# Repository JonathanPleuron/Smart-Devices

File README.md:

## Smart Gas Sensor

This project was realised in the IoT growing context. It introduces a solution of 
smart gas sensor using the emerging LoRa technology.

### Code 

See the arduino section for the sensor relative implementation (low level).
See the JAVA section for application (high level).

### Documentation

See documentation folder for global documentation about the project and useful datasheets

### PCB

A PCB was designed for the Smart sensor (Uses [KiCad](http://kicad-pcb.org/) free software)

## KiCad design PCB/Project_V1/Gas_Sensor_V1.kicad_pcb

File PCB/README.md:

## PCB conception

The PCB for the projet "Smart gas sensor" was designed using the free software Kicad.

### Presentation

See PCB_Kicad.pdf

### Sources

The available sources are :

	- Project_V1 : Kicad source files (Schematic, footprints, Netlist, PCB)
	- MyLib : Library for specifically designed components

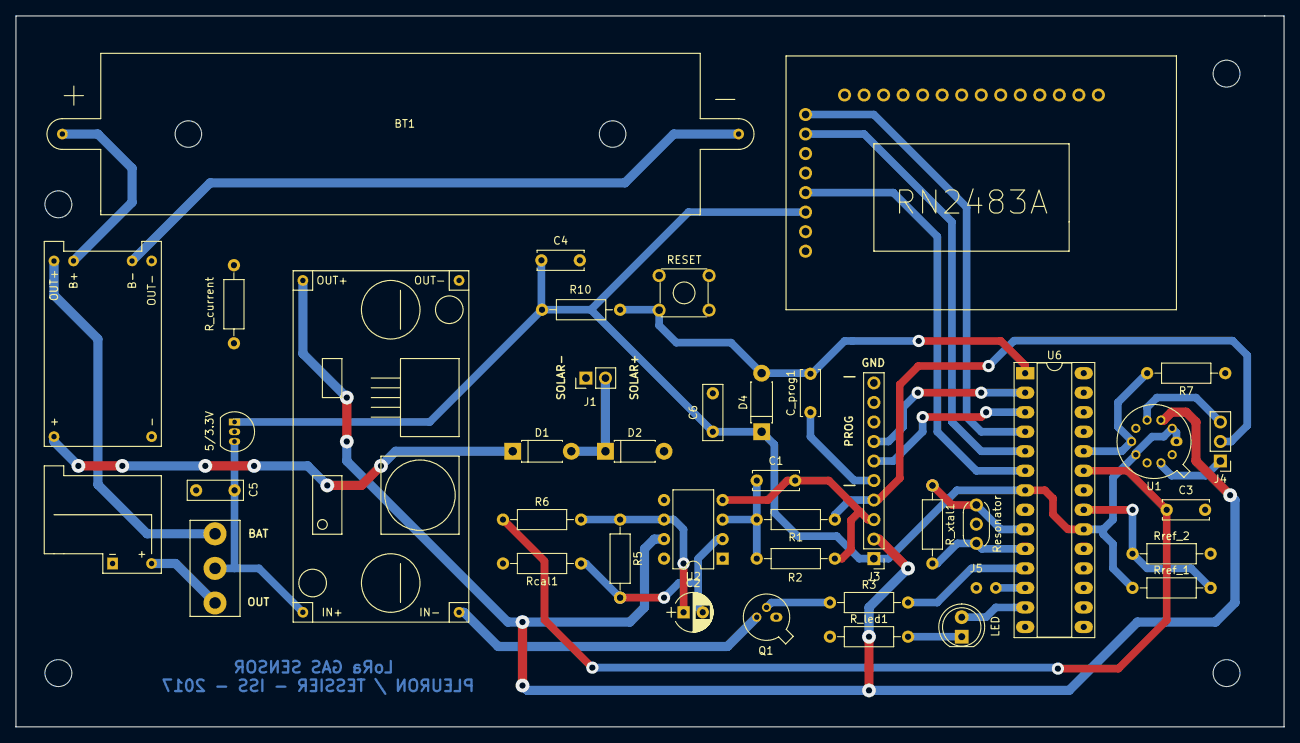
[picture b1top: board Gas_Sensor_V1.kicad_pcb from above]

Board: 2 copper layers, 165.0 x 92.5 mm, 38 parts (0 on the bottom side), 29 nets.

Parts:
5/3.3V: L78L33_TO92; TO-92_Inline_Narrow_Oval
BT1: 3.6V; BatterieSupport
C1, C3, C4: 100n; C_Disc_D6.0mm_W2.5mm_P5.00mm
C2: 1u; CP_Radial_D5.0mm_P2.50mm
C5: 330n; C_Rect_L7.2mm_W2.5mm_P5.00mm_FKS2_FKP2_MKS2_MKP2
C6: 100n; C_Rect_L7.2mm_W2.5mm_P5.00mm_FKS2_FKP2_MKS2_MKP2
C_prog1: 100n; C_Disc_D6.0mm_W2.5mm_P5.00mm
D1, D2: D; D_DO-41_SOD81_P7.62mm_Horizontal
D4: D_DO-41_SOD81_P7.62mm_Horizontal
J1: Socket_Strip_Straight_1x02_Pitch2.54mm
J3: Socket_Strip_Straight_1x10_Pitch2.54mm
J4: Pin_Header_Straight_1x03_Pitch2.54mm
J5: PAD_02
LED: LED_D5.0mm
Q1: PN2222A; TO-18-3
R1, R10: 10k; R_Axial_DIN0207_L6.3mm_D2.5mm_P10.16mm_Horizontal
R2, R5: 100k; R_Axial_DIN0207_L6.3mm_D2.5mm_P10.16mm_Horizontal
R3, R6: 1k; R_Axial_DIN0207_L6.3mm_D2.5mm_P10.16mm_Horizontal
R7: R; R_Axial_DIN0207_L6.3mm_D2.5mm_P10.16mm_Horizontal
RESET: SW_PUSH; SW_TH_Tactile_Omron_B3F-10xx
R_current: R_Axial_DIN0207_L6.3mm_D2.5mm_P10.16mm_Horizontal
R_led1: 150; R_Axial_DIN0207_L6.3mm_D2.5mm_P10.16mm_Horizontal
R_xtal1: 1meg; R_Axial_DIN0207_L6.3mm_D2.5mm_P10.16mm_Horizontal
Rcal1: R_Axial_DIN0207_L6.3mm_D2.5mm_P10.16mm_Horizontal
Resonator: Resonator-3pin_w6.0mm_h3.0mm
Rref_1, Rref_2: R_Axial_DIN0207_L6.3mm_D2.5mm_P10.16mm_Horizontal
U1: TO-78-10
U2: LTC1050; DIP-8_W7.62mm
U5: 3V6_to_10V_stepup; DC_DC_stepup
U6: ATMEGA328P-PU; DIP-28_W7.62mm_Socket_LongPads
U7: RN2483_BREAKOUT

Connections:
3V3: 5/3.3V.1, C4.1, C6.1, D4.1, J3.1, R10.1, Rref_1.1, U1.1, U1.2, U1.7, U6.7, U6.20, U7.19
10V: J3.2, U1.3, U2.7, U5.3
/ADC_GAS: C3.1, R6.1, U6.23
/ADC_temp: R7.2, U1.6, U6.24
/DRT_PROG: C_prog1.1, J3.5
/LoRa_RST: U6.6, U7.18
/LoRa_RX: U6.5, U7.15
/LoRa_TX: U6.4, U7.14
/Push_button: J5.1, U6.12
/RESET: C_prog1.2, D4.2, R10.2, RESET.1, RESET.3, U6.1
/RX_PROG: J3.6, U6.3
/SOLAR+: D1.2, D2.1, J1.2
/TX_PROG: J3.7, U6.2
/XTAL1: R_xtal1.1, Resonator.1, U6.9
/XTAL2: R_xtal1.2, Resonator.3, U6.10
/gas_sig: J3.4, J4.2, R1.1
/heat: R3.2, U6.11
GND: 5/3.3V.2, C1.2, C3.2, C4.2, C5.2, C6.2, D2.2, J1.1, J3.3, J3.10, J5.2, Q1.1, R2.2, R7.1, RESET.2, RESET.4, R_current.2, R_led1.1, Rcal1.2, Resonator.2, Rref_2.2, U1.8, U2.4, U5.4, U6.8, U6.22, U7.21
unnamed: C1.1, R1.2, R2.1, U2.3
unnamed: C2.1, R5.1, R6.2, U2.6
unnamed: C2.2, R5.2, Rcal1.1, U2.2
unnamed: 5/3.3V.3, C5.1, U5.1
unnamed: LED.1, R_led1.2
unnamed: LED.2, U6.13
unnamed: J4.1, U1.9
unnamed: J4.3, U1.4
unnamed: Q1.2, R3.1
unnamed: Q1.3, U5.2
unnamed: Rref_1.2, Rref_2.1, U6.21

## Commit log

2018-01-28 Add readme + code + documentation
